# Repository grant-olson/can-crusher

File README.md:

Welcome to the repository for the most sophisticated robotic aluminum
can crusher that the world has seen!

This is the result of a hobby project that combines CAD design,
Hardware, PCB design, firmware, and software to build an over-the-top
computer-controlled can crusher. I wanted to use a wide variety of skills
on this project instead of going deep into a specific skill.

## In depth 30 minute video on the project

[The Most Technologically Advanced Aluminum Can Crusher In The World](https://youtu.be/nmYN3EZNI_g)

## The Frame

The frame starts with 3 standard 2040 slotted aluminum extrusions. From there
the major structural elements, the:

* top
* bottom
* crusher plate

Are made from laser cut aluminum.

The rest of the parts are 3D printed.

All design elements are in the included FreeCAD workspace. If you just
want to cut or print the parts refer to the [stl directory](./stl) for
3D print files or the [step directory](./step) for files suitable for laser
cutting.

You will also need two stepper motors with rods and two smooth rods to
assemble the frame in its entirety.

## Stepper Control Board

To drive the stepper motors I've made a control board powered by a Raspberry
Pi Pico that uses TMC2209 chips to drive the steppers. This allows me to
auto-detect limits of movement.

The design is in KiCad. Gerber files are also included in the repo for
getting PCBs made.

At a high level the control board:

* Initializes the system
* Accepts a small command language over the UART interface.
* Controls the motors appropriately.

I chose the Pi Pico so that I could use the PIO subprocessors to get
extremely reliable control of the stepper signal waves. I'm able to
run those completely deterministicly based on the clock speed where
even IRQs won't affect triggering.

To build the software:

* Set up your computer to build for Pico projects.
* `cd firmware/pico`
* `mkdir build`
* `cd build`
* `cmake ..`
* `make`
* `picotool load can-crusher.uf2 && picotool reboot`

If you have stepper motors hooked up they should perform a minor
up/down jogging of the motors upon reboot. Use this to see if the
code is actually running without the admin consoles set up.

## High level control and UI

For the high level control and UI I've written a program for a Raspberry
Pi that shows a minimal display on a TFT-LCD with touchscreen to allow users
to interact.

To make a compact display I've created a Hat for a Pi Zero board that allows
you to mount the parts together directly that is also released as a KiCad file.

Due to continuing Raspberry Pi shortages I'd like to build some
alternate versions of the control boards for other SBCs. The software
itself iswritten in python and should be portable to pretty much any
linux system. There are only 3 hardware requirements so I expect other
boards will be easy to integrate:

* Ability to have a hardware level SPI control with /dev/spidevX.X exposed.

* A kernel that supports ADS7846  touch screens and provides integration with
    `evdev` to read touch screen events.

* A hardware serial/uart port capable of running at 115200 baud.

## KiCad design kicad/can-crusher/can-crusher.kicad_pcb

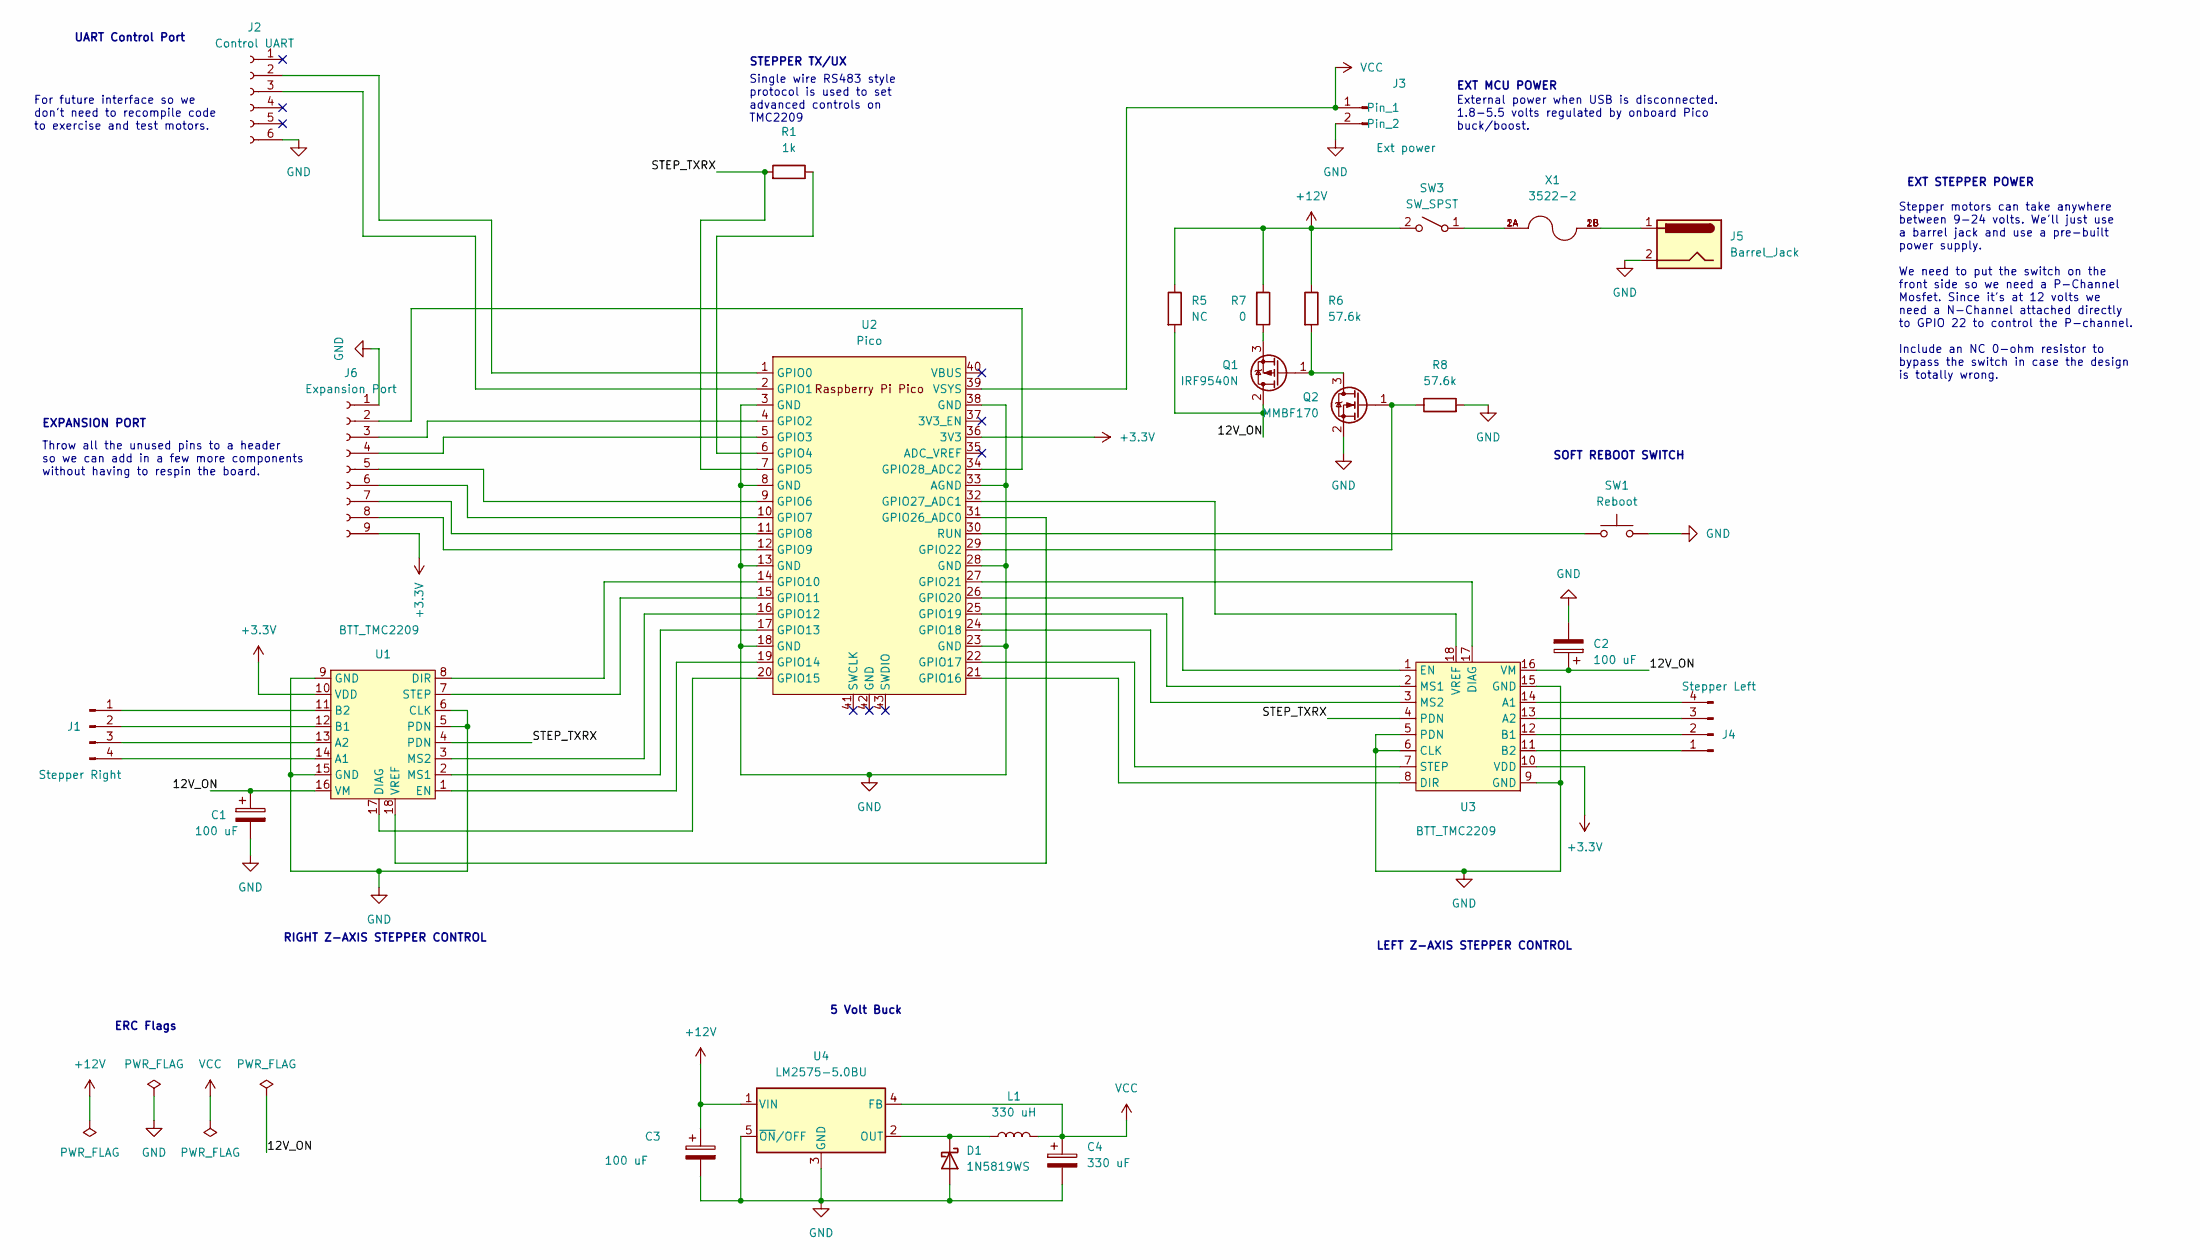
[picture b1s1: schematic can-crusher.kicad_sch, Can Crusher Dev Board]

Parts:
C1, C2, C3: 100 uF; CP_Radial_D6.3mm_P2.50mm
C4: 330 uF; CP_EIA-7343-43_Kemet-X
D1: 1N5819WS; D_SOD-323
J1: Stepper Right; JST_XH_B4B-XH-A_1x04_P2.50mm_Vertical
J2: Control UART; PinSocket_1x06_P2.54mm_Vertical
J3: Ext power; PinHeader_1x02_P2.54mm_Vertical
J4: Stepper Left; JST_XH_B4B-XH-A_1x04_P2.50mm_Vertical
J5: Barrel_Jack; BarrelJack_CUI_PJ-063AH_Horizontal
J6: Expansion Port; PinSocket_1x09_P2.54mm_Vertical
L1: 330 uH; L_Radial_D12.0mm_P5.00mm_Fastron_11P
Q1: IRF9540N; TO-220-3_Vertical
Q2: MMBF170; SOT-23
R1: 1k; R_0805_2012Metric
R5: NC; R_1206_3216Metric
R6: 57.6k; R_1206_3216Metric
R7: 0; R_1206_3216Metric
R8: 57.6k; R_0805_2012Metric
SW1: Reboot; SW_PUSH_6mm_H4.3mm
SW3: SW_SPST; SW_R1966ABLKBLKGR
U1, U3: BTT_TMC2209
U2: Pico; RPi_Pico_SMD_TH
U4: LM2575-5.0BU; TO-263-5_TabPin3
X1: 3522-2; FUSE_3522-2; PARTREV J

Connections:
+3.3V: J6.9, U1.10 (VDD), U2.36 (3V3), U3.10 (VDD)
+12V: C3.1, R5.1, R6.1, R7.2, SW3.2 (B), U4.1 (VIN)
/12V_ON: C1.1, C2.1, Q1.2 (D), R5.2, U1.16 (VM), U3.16 (VM)
/STEP_TXRX: R1.2, U1.4 (PDN), U2.7 (GPIO5), U3.4 (PDN)
GND: C1.2, C2.2, C3.2, C4.2, D1.2 (A), J2.6, J3.2, J5.2, J6.1, Q2.2 (S), R8.2, SW1.2, U1.5 (PDN), U1.6 (CLK), U1.9 (GND), U1.15 (GND), U2.3 (GND), U2.8 (GND), U2.13 (GND), U2.18 (GND), U2.23 (GND), U2.28 (GND), U2.33 (AGND), U2.38 (GND), U3.5 (PDN), U3.6 (CLK), U3.9 (GND), U3.15 (GND), U4.3 (GND), U4.5 (~ON/OFF)
unnamed: D1.1 (K), L1.1, U4.2 (OUT)
unnamed: J1.1, U1.11 (B2)
unnamed: J1.2, U1.12 (B1)
unnamed: J1.3, U1.13 (A2)
unnamed: J1.4, U1.14 (A1)
unnamed: J2.2, U2.1 (GPIO0)
unnamed: J2.3, U2.2 (GPIO1)
unnamed: J4.1, U3.11 (B2)
unnamed: J4.2, U3.12 (B1)
unnamed: J4.3, U3.13 (A2)
unnamed: J4.4, U3.14 (A1)
unnamed: J5.1, X1.1B, X1.2B
unnamed: J6.2, U2.34 (GPIO28_ADC2)
unnamed: J6.3, U2.4 (GPIO2)
unnamed: J6.4, U2.5 (GPIO3)
unnamed: J6.5, U2.9 (GPIO6)
unnamed: J6.6, U2.10 (GPIO7)
unnamed: J6.7, U2.11 (GPIO8)
unnamed: J6.8, U2.12 (GPIO9)
unnamed: Q1.1 (G), Q2.3 (D), R6.2
unnamed: Q1.3 (S), R7.1
unnamed: Q2.1 (G), R8.1, U2.29 (GPIO22)
unnamed: R1.1, U2.6 (GPIO4)
unnamed: SW1.1, U2.30 (RUN)
unnamed: SW3.1 (A), X1.1A, X1.2A
unnamed: U1.1 (EN), U2.19 (GPIO14)
unnamed: U1.2 (MS1), U2.17 (GPIO13)
unnamed: U1.3 (MS2), U2.16 (GPIO12)
unnamed: U1.7 (STEP), U2.15 (GPIO11)
unnamed: U1.8 (DIR), U2.14 (GPIO10)
unnamed: U1.17 (DIAG), U2.20 (GPIO15)
unnamed: U1.18 (VREF), U2.31 (GPIO26_ADC0)
unnamed: U2.21 (GPIO16), U3.8 (DIR)
unnamed: U2.22 (GPIO17), U3.7 (STEP)
unnamed: U2.24 (GPIO18), U3.3 (MS2)
unnamed: U2.25 (GPIO19), U3.2 (MS1)
unnamed: U2.26 (GPIO20), U3.1 (EN)
unnamed: U2.27 (GPIO21), U3.17 (DIAG)
unnamed: U2.32 (GPIO27_ADC1), U3.18 (VREF)
VCC: C4.1, J3.1, L1.2, U2.39 (VSYS), U4.4 (FB)

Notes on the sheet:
STEPPER TX/UX
ERC Flags
EXT MCU POWER
External power when USB is disconnected. 1.8-5.5 volts regulated by onboard Pico buck/boost.
LEFT Z-AXIS STEPPER CONTROL
EXPANSION PORT
Stepper motors can take anywhere between 9-24 volts. We'll just use a barrel jack and use a pre-built power supply. We need to put the switch on the front side so we need a P-Channel Mosfet. Since it's at 12 volts we need a N-Channel attached directly to GPIO 22 to control the P-channel. Include an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
For future interface so we don't need to recompile code to exercise and test motors.
Throw all the unused pins to a header so we can add in a few more components without having to respin the board.
UART Control Port
5 Volt Buck
EXT STEPPER POWER
RIGHT Z-AXIS STEPPER CONTROL
SOFT REBOOT SWITCH
Single wire RS483 style protocol is used to set advanced controls on TMC2209

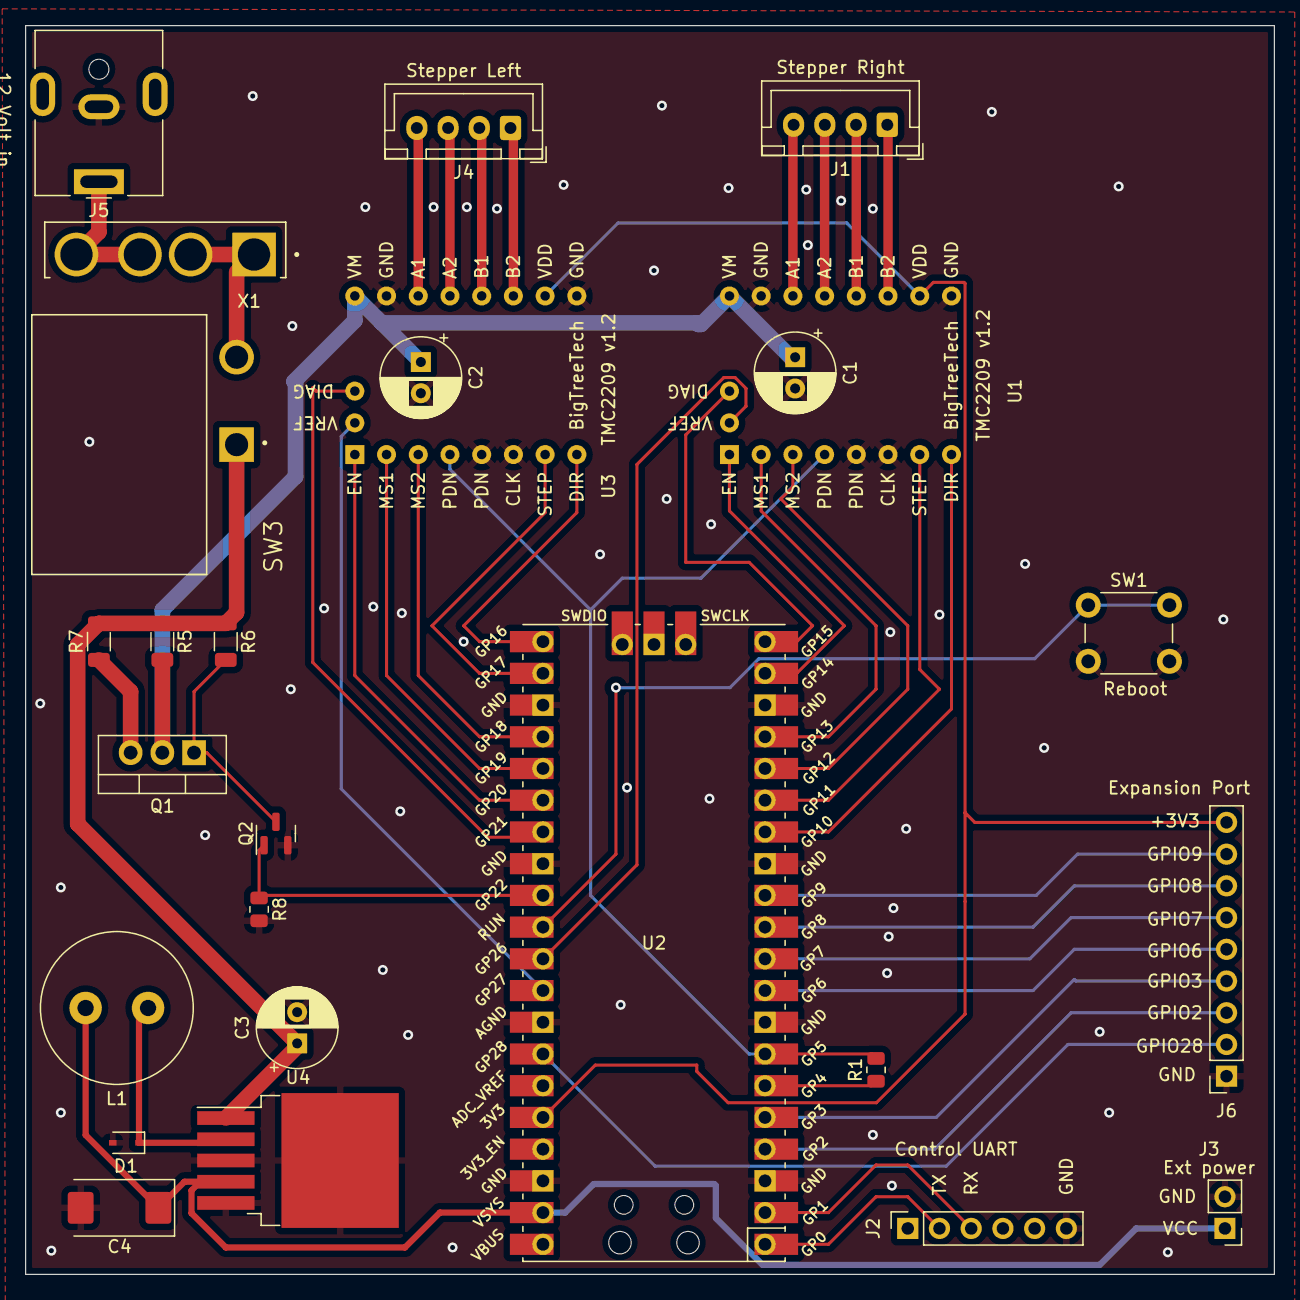
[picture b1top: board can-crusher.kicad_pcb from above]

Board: 2 copper layers, 100.0 x 100.0 mm, 26 parts (0 on the bottom side), 45 nets.

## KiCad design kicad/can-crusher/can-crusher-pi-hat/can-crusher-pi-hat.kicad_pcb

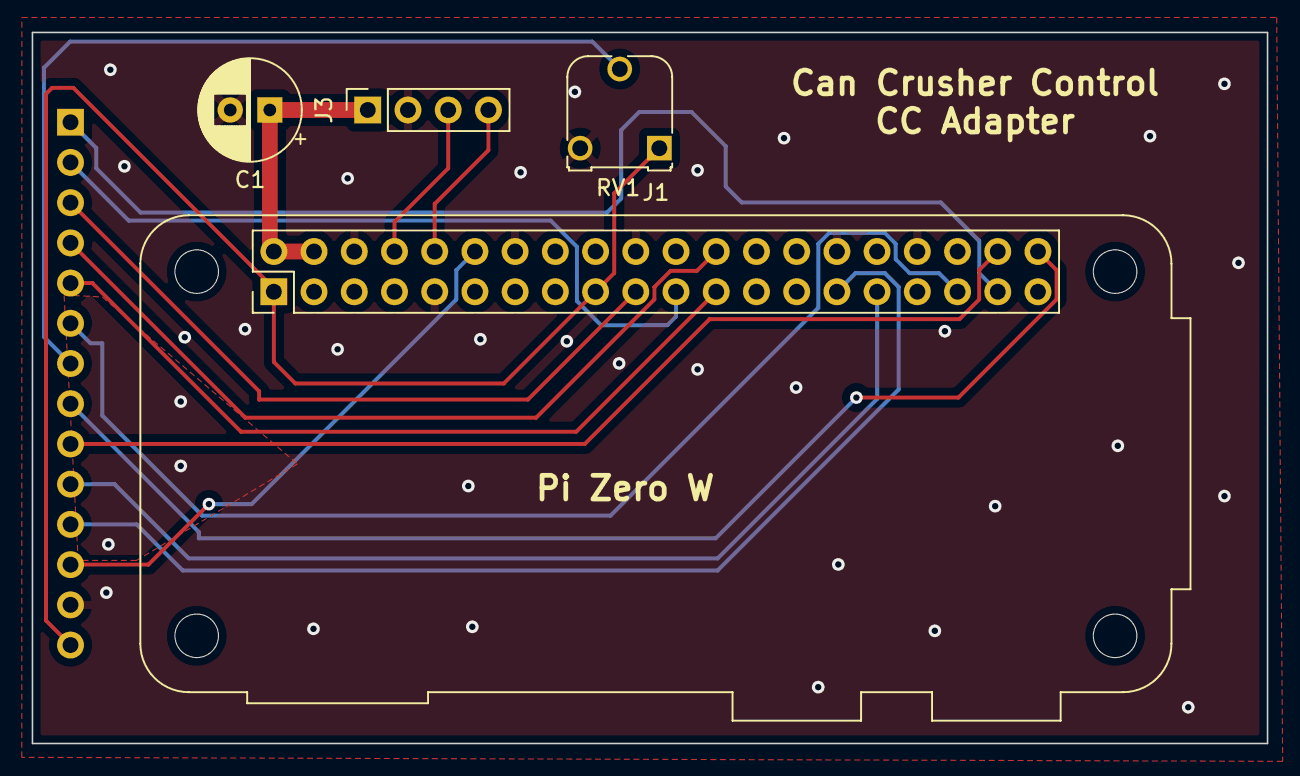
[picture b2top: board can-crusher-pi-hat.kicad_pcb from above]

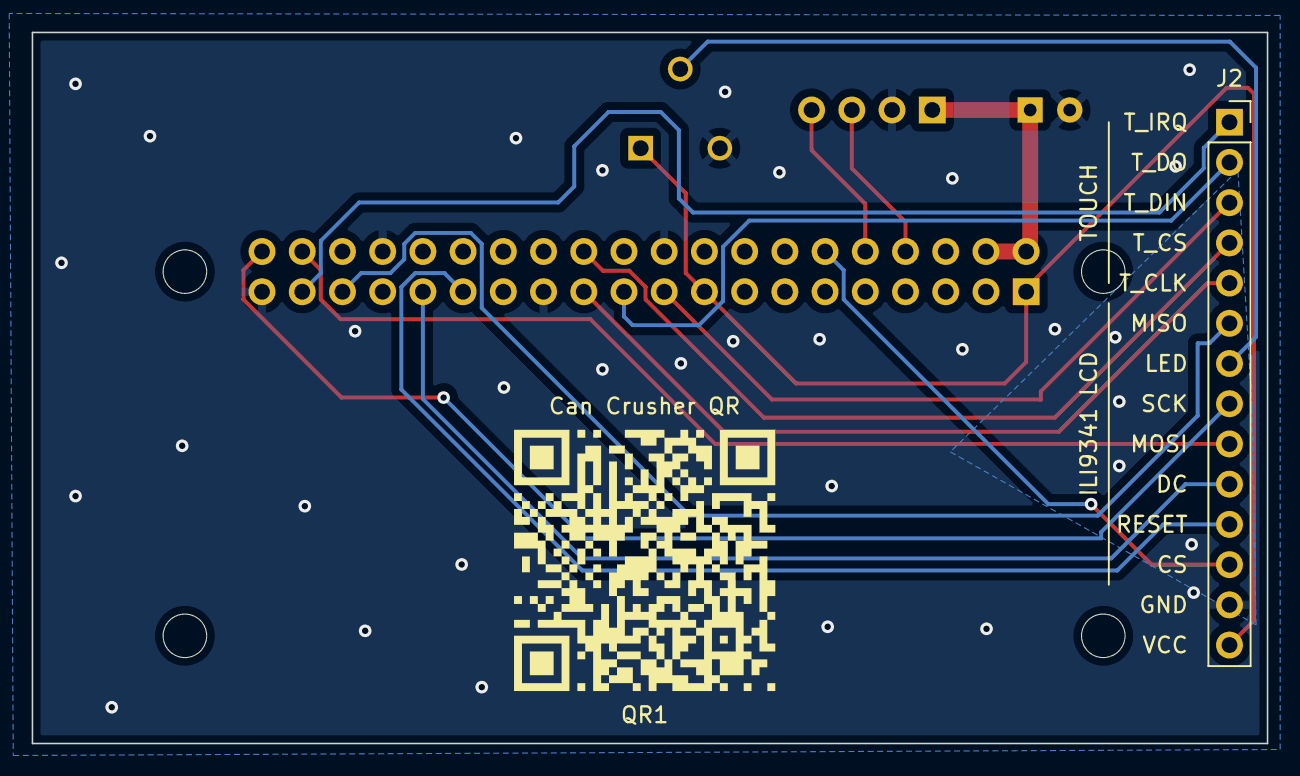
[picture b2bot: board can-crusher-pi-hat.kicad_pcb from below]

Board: 2 copper layers, 78.0 x 44.9 mm, 6 parts (3 on the bottom side), 17 nets.

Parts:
C1: C_Polarized; CP_Radial_D6.3mm_P2.50mm
J1: Raspberry_Pi_2_3; Raspberry_Pi_Zero_Socketed_THT_FaceDown_MountingHoles
J2: ILI9341_LCD_TouchScreen; PinSocket_1x14_P2.54mm_Vertical
J3: Pico_Connector; PinSocket_1x04_P2.54mm_Vertical
QR1: Can Crusher QR
RV1: R_Potentiometer; Potentiometer_Runtron_RM-065_Vertical

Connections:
+3V3: J1.1 (3V3), J1.17 (3V3), J2.14 (3V3_VCC), RV1.1
+5V: C1.1, J1.2 (5V), J1.4 (5V), J3.1 (+5V_IN)
GND: C1.2, J1.6 (GND), J1.9 (GND), J1.14 (GND), J1.20 (GND), J1.25 (GND), J1.30 (GND), J1.34 (GND), J1.39 (GND), J2.13 (GND), J3.2 (GND), RV1.3
unnamed: J1.8 (GPIO14/TXD), J3.3 (TX)
unnamed: J1.10 (GPIO15/RXD), J3.4 (RX)
unnamed: J1.12 (GPIO18/PWM0), J2.12 (LCD_CS)
unnamed: J1.19 (MOSI0/GPIO10), J2.3 (Touch_MOSI)
unnamed: J1.21 (MISO0/GPIO9), J2.2 (TOUCH_MISO)
unnamed: J1.23 (SCLK0/GPIO11), J2.5 (Touch_CLK)
unnamed: J1.24 (~CE0/GPIO8), J2.4 (Touch_CS)
unnamed: J1.29 (GCLK1/GPIO5), J2.11 (LCD_RESET)
unnamed: J1.31 (GCLK2/GPIO6), J2.10 (LCD_DC)
unnamed: J1.35 (GPIO19/MISO1), J2.6 (LCD_MISO)
unnamed: J1.37 (GPIO26), J2.1 (Touch_IRQ)
unnamed: J1.38 (GPIO20/MOSI1), J2.9 (LCD_MOSI)
unnamed: J1.40 (GPIO21/SCLK1), J2.8 (LCD_CLK)
unnamed: J2.7 (LCD_BKLIGHT), RV1.2

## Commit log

2022-09-27 Initial checkin of FreeCAD files
2022-09-27 Add test for parts that must go in to extruded rails
2022-09-27 Initial stepper holders
2022-09-27 Rod holder parts
2022-09-28 Add screw counter-sinks
2022-09-28 Add 3d printed base to go under CNCed base, so we can countersink installation screws and add feet to the base.
2022-09-29 Add bill of materials
2022-09-29 Finish up servo holder add mounting holes for M3 screws
2022-09-29 Chamfer body feet
2022-09-29 Fix servo holder hole which got filled back in.
2022-09-30 More refinements to design
2022-10-02 Match acrylic parts to thickness of my stock. Save good copies as step for ease in CNC path layout
2022-10-04 Skeleton application fro Pi Pico firmware development
2022-10-04 Quick and dirty motor test
2022-10-04 Basic motor api
2022-10-05 Basic ping of UART interface
2022-10-05 Actually read registers from TMC2209
2022-10-06 Write to TMC2209 registers
2022-10-07 Adjust crusher plate to work with motors.
2022-10-07 Write functions so that motors act in lock step in main body
2022-10-07 Stall Detection, left motor only.
2022-10-07 Move MS1 and MS2 to gpio
2022-10-07 All code to detect stalls on both motors
2022-10-07 Add motor_move_mm call to simplify motion
2022-10-07 Basic homing code. Need to figure out why stall status isn't clearing out on motor reset
2022-10-07 Add step file of cnc test part
2022-10-07 Step file for crusher element
2022-10-07 Rotated crusher element
2022-10-09 Test part to add weight to crusher element
2022-10-09 Change cad dir to differentiate from KiCad PCB directory
2022-10-10 Initial kicad project with external Pi Pico reference
2022-10-10 Added pico to schematic, really just testing that git works well between OSes
2022-10-10 Change external repo to fork with fixes
2022-10-10 Schematic Work in progress
2022-10-10 Schematic work-in-progress checkpoint
2022-10-10 Update external Pico library refs
2022-10-10 Initial first pass of PCB design
2022-10-11 Added title comments, etc, to title block
2022-10-11 Add BigTreeTech TMC2209 symbol
2022-10-11 Fix VREF setting on Pico layout
2022-10-11 Fixes for ERC checks
2022-10-11 Add can holder at base so can doesn't pop out
2022-10-11 Basic footprint for BigTreeTech board
2022-10-11 More tweaks to 12 enable circuitry;First round of assigning all footprints
2022-10-11 Rough out initial rats nest; Change pin assignments to make layout easier.
2022-10-11 Give better name to project lib storage dir
2022-10-12 Make board more compact; make power traces appropriate sized.
2022-10-12 Global .gitignore
2022-10-12 Final REV 1 control board submitted for PCB manufacturing
2022-10-12 Include headers in printout
2022-10-13 PCB Vendor requested 0.5mm spacing between RGB LED holes by making holes 0.75mm instead of 0.9mm
2022-10-14 Modify crusher design for laser cut aluminum
2022-10-15 Servo holders needed clearance for JST connector
2022-10-17 Fix pin assignments based on new schmatic.
2022-10-17 Test optional power and fix problem with new pin assignment, test motors
2022-10-17 Test of RGB led and user button
2022-10-18 Move motor code in to module
2022-10-18 Fix initialization sequence. Fix bug in speeds running both motors at once
2022-10-18 Move power code to module; have motor control init check to see that motors are powered
2022-10-18 Have all _init methods return success/failure codes, and check these, even if they're not needed yet
2022-10-18 Export stl with tapered base feet
2022-10-18 Serial connection that echos back text. No cmd processor yet.
2022-10-18 Basic serial cmd processor with VERSION, ECHO, and MOVE commands.
2022-10-18 Debounce stall detection until we figure out how to correctly clear stalls.
    Handle motor subsystem with motors_wake and motors_sleep.
    Add WAKE and SLEEP commands to the Serial CLI.
2022-10-18 Handle backspaces when reading serial input
2022-10-18 Clean up boot initialization code now that we have a CLI
2022-10-18 Clean up auto homing code
2022-10-18 Add serial_flush() method to clear out garbage when activating the serial CLI
2022-10-18 CLI commands to cut and restore 12 volt power
2022-10-19 Add MOVE_LEFT and MOVE_RIGHT with limited motion to level
2022-10-19 Check power and wake states before moving
2022-10-19 Add basic homing
2022-10-19 Treat motor stalling as an error condition in the CLI
2022-10-19 Move serial error codes to header file
2022-10-19 Have version cli return value use same api style as position
2022-10-19 Leave motor position as unknown until we explicitly home
2022-10-19 Allow manual zeroing of position
2022-10-19 make more specific stall warnings telling the trigger.
2022-10-19 Simpler logic for problem where motors stall immediately
2022-10-19 Position tracking should assume left and right movements are wiggling and levelling the platform, not changing absolute position.
2022-10-19 Initial case for dev PCB
2022-10-19 Old rod support was too tight and sqeaky. Give some more tolerance in the hole. Make it longer to compensate. Allow user to see the screw through the top opening.
2022-10-19 Ignore non-printable characters
2022-10-19 Give 12V power control commands names more in line with other commands
2022-10-19 Add latest blog post to the README
2022-10-20 Add build id to boot prompt.
2022-10-20 Add build id to USB logs
2022-10-20 Add facility to store values as properties, use them for the stallguard settings in the motor unit, allow users to get and set properties in serial console.
2022-10-20 Improve homing. Allow homing to report a failure
2022-10-21 Move step settings and stallguard enable settings to properties
2022-10-21 Give TMC2209 variable names better names than the datasheet abbreviated names
2022-10-21 Auto capitalize anything sent to the serial console
2022-10-21 Don't turn on green light
2022-10-24 Make pcb case thinner, and assume we're surface mounting the Pico
2022-10-24 Initial python scripts to test firmware
2022-10-24 Add pull down to power circuitry
2022-10-24 Add mounting holes
2022-10-25 Make home parameters tunable; add cli method RESET_PROPS to restore factory defaults
2022-10-25 Improve script that profiles stallguard numbers
2022-10-26 Allow for tracking of negative positions from zero position. Allow serial CLI to get sentinel value indicating if we are actually UNHOMED
2022-10-27 Fix compiler warning
2022-10-27 Initial integration of pio based stepper clock for greater accuracy
2022-10-27 Proper tuning of TCOOLTRSH fixes the issue where motors stall on initial movement
2022-10-27 Track distance, detect proper stalls, in pop motor movement
2022-10-27 Remove debug prints
2022-10-27 Add left/right movements to PIO based movement
2022-10-27 Improve homing
2022-10-28 Load/Save properties to last sector in flash
2022-10-31 Have home use home_speed everywhere
2022-10-31 Tweaks to make sure Rod holder and servo holder line up with crusher plate
2022-11-02 Vertical bearing holder for smooth rods
2022-11-02 Modified crusher element for smooth rods
2022-11-02 Add another .gitignore
2022-11-02 Modify can holder to also hold smooth rods
2022-11-06 Screw holes on vertical bearing holder were a little too close to the edge.
2022-11-07 Proper top holder for smooth rods.
2022-11-07 Stop keeping freecad backups in git, its redundant
2022-11-07 Clean up full cad view to reflect current design.
2022-11-07 Update to newest can holder
2022-11-07 Ignore backups
2022-11-08 Stabilize stallguard test code
2022-11-08 Use home_speed for jogging code when can crusher boots
2022-11-08 Fixes for binding stepper motion:
    1. Put slots instead of holes on the stepper holder so we can manually true it.
    2. Rod holders SHOULD allow a lot of play, and just stop rods when something has gone horribly wrong.
2022-11-08 Give stepper holder stl correct name
2022-11-08 Make sure int values are ints, atoi() doesn't have error conditions
2022-11-08 Don't allow move speed of zero in serial interface
2022-11-10 Make find_stallguard_point a self contained program
2022-11-10 Script updates
2022-11-10 Start moving to SMD components
2022-11-11 Another blog post in readme
2022-11-11 Add power management so we don't burn out steppers
2022-11-11 Add new serial commands to python interface
2022-11-11 Remove buffer space on smooth rod holders. The rods would move around.
2022-11-11 Script to crush cans
2022-11-11 Add real can crusher pic to readme
2022-11-11 Include link to latest build post
2022-11-12 Add missing header
2022-11-14 Initial holder for control computer
2022-11-14 Initial test CLI user interface before GUI based UI
2022-11-16 Script to make images for display
2022-11-16 Add drivers for Raspberry Pi hardware
2022-11-16 Move all python scripts to the control software directory
2022-11-16 Move slide-maker fiels in to subdirectories
2022-11-17 Rename some board files now that we have two boards.
2022-11-17 Display PCB hat to connect Pi Zero and TFT LCD
2022-11-17 Final dial in of touch screen holder settings
2022-11-18 Add calibration and local coordinate lookup to touch screen interface
2022-11-18 Ignore more kicad backups
2022-11-18 Start beefing up the README
2022-11-18 Add picture of touchscreen display
2022-11-18 Control PCBA picture
2022-11-18 Quick and Dirty Pi implementation
2022-11-19 Persistant configuration
2022-11-19 Move library code to a package, and only have executables in main interface directory
2022-11-19 Give ui software directory a better name; control software can be confused with the embedded software
2022-11-19 Fix import after moving code to package
2022-11-19 Make slide-maker executable
2022-11-20 More slide types and code cleanup
2022-11-20 Make directories if they don't exist
2022-11-20 Add environment variable to disable homing on boot of UX, because that slows develepment cycles
2022-11-20 get slides from the right directory and show them in the right order
2022-11-21 Slide Maker should make admin screens
2022-11-21 Basic logic to show messages when working
2022-11-21 Make sure we're powered on when running the UI
2022-11-21 Give some time for full spidev setup by OS so we can start as a service
2022-11-21 Example file for systemd service
2022-11-21 Adjust spi display for current screen orientation.
2022-11-21 Move PiHat folder to a sibling folder of original KiCad project
2022-11-21 Fixed stupid, stupid wiring error with serial control. Reverted screen to normal position and have pi use /dev/serial0
2022-11-21 More improvements to PCB holder
2022-11-21 Production PCB lid, no big gap to access dev buttons
2022-11-22 Move all the slide pregeneration code to a DisplayHelper class
2022-11-22 Fixes for slide refactor
2022-11-22 Test to make sure we talk to Pico. Throw error if we're not connected
2022-11-22 Add more fun and entertaining aluminum facts
2022-11-22 Actually... lets always try to show a failure screen for any failure
2022-11-22 Catch another error case
2022-11-22 Add missing comma
2022-11-22 Increase wall thickness on power plug hole
2022-11-23 Fix typo
2022-11-23 Readme for ui-software
2022-11-23 Better stuff in BoM
2022-11-23 Code to allow premade images as slides
2022-11-24 Add fuse, power switch, and electrolytic caps
2022-11-24 Remove RGB led and button; add free pins to header; add ADC pins to the TMC2209 VREF pins for future use
2022-11-24 More tuning on alt pcb holder
2022-11-24 Renamed alternate parts to make it clear you should print one or the other
2022-11-25 Rev 2 of control PCB
2022-11-25 Add explanation for Symbols and Footprints we can't include in our git repo.
2022-11-25 Notes on head board requirements
2022-11-25 Move gerbers to top level directory so they're easy to find, and in the same basic area users will find STL and STEP files
2022-12-11 Remove ads
2023-01-12 Include link to video in README
2024-01-12 Allow config to store individual unit's stallguard threshold
2024-01-12 Always set ui.stallguard_threshold
2024-01-12 New homing strategy. Don't try to be too smart. Just go til we stall 4 times, assuming the rails get closer each time.
